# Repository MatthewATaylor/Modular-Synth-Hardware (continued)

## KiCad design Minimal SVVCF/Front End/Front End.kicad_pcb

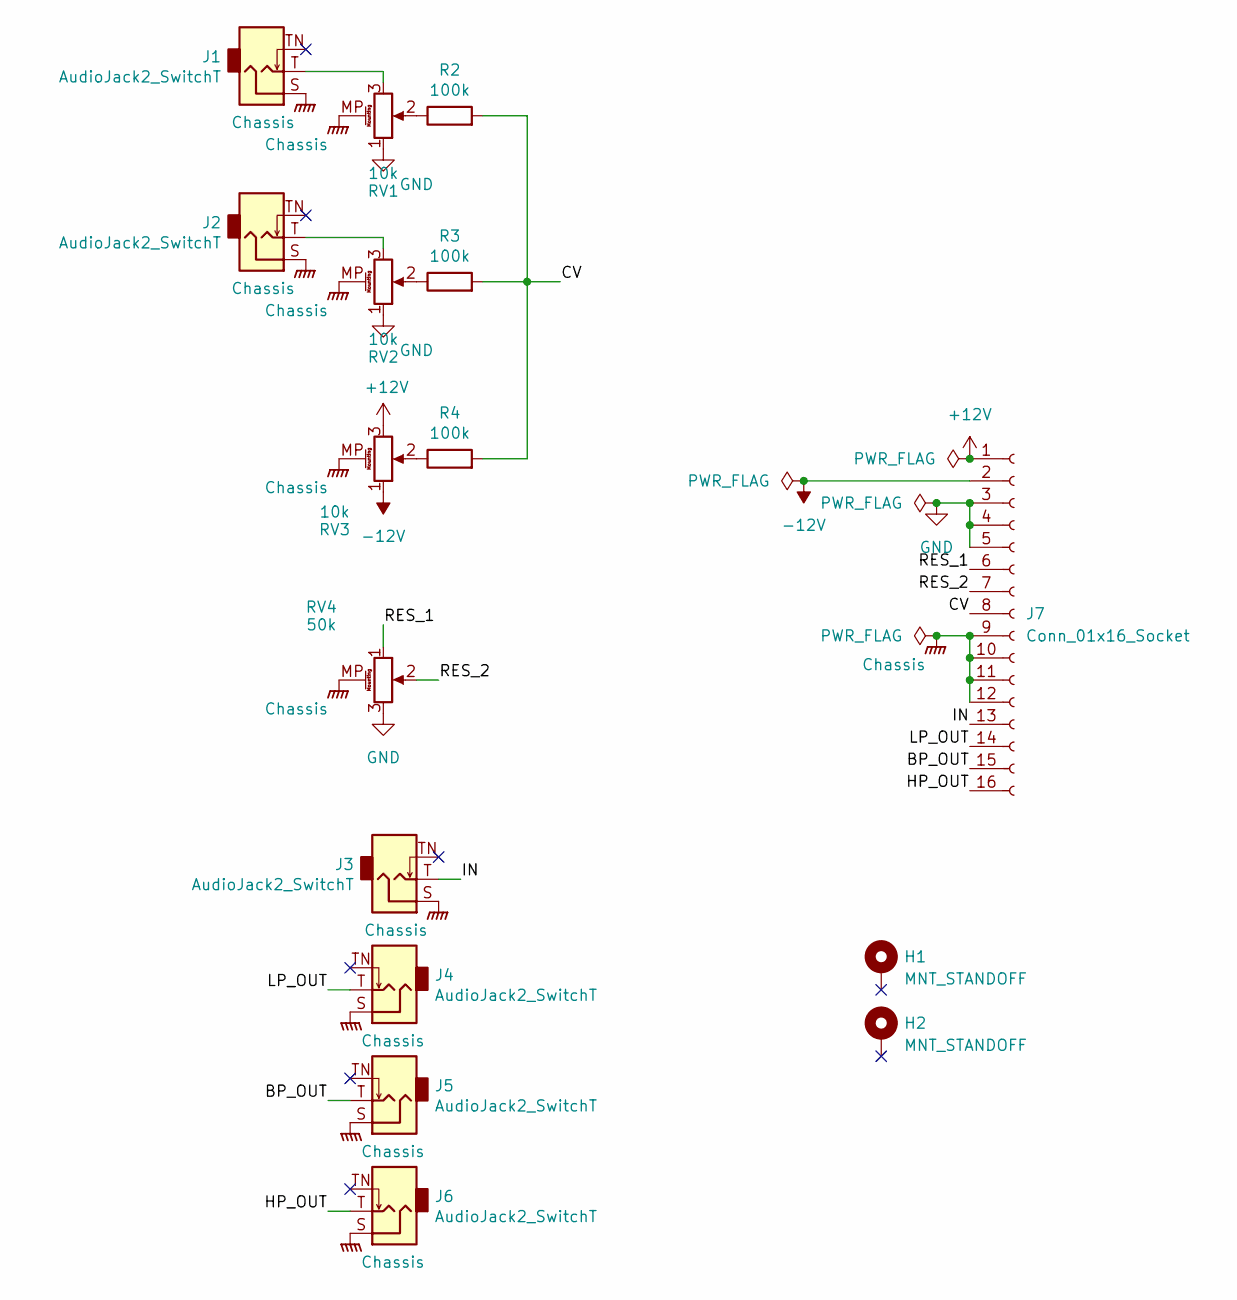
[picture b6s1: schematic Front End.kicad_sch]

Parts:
H1, H2: MNT_STANDOFF; MountingHole_Pitch7.5mm_Drill3.4mm
J1, J2, J3, J4, J5, J6: AudioJack2_SwitchT; Jack_3.5mm_QingPu_WQP-PJ398SM_Vertical_CircularHoles
J7: Conn_01x16_Socket; PinHeader_1x16_P2.54mm_Vertical
R2, R3, R4: 100k; R_Axial_DIN0207_L6.3mm_D2.5mm_P7.62mm_Horizontal
RV1, RV2, RV3: 10k; Potentiometer_Alpha_RD901F-40-00D_Single_Vertical_MP
RV4: 50k; Potentiometer_Alpha_RD901F-40-00D_Single_Vertical_MP

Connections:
+12V: J7.1, RV3.3
-12V: J7.2, RV3.1
/BP_OUT: J5.T, J7.15
/CV: J7.8, R2.2, R3.2, R4.2
/HP_OUT: J6.T, J7.16
/IN: J3.T, J7.13
/LP_OUT: J4.T, J7.14
/RES_1: J7.6, RV4.1
/RES_2: J7.7, RV4.2
Chassis: J1.S, J2.S, J3.S, J4.S, J5.S, J6.S, J7.9, J7.10, J7.11, J7.12, RV1.MP (MountPin), RV2.MP (MountPin), RV3.MP (MountPin), RV4.MP (MountPin)
GND: J7.3, J7.4, J7.5, RV1.1, RV2.1, RV4.3
unnamed: J1.T, RV1.3
unnamed: J2.T, RV2.3
unnamed: R2.1, RV1.2
unnamed: R3.1, RV2.2
unnamed: R4.1, RV3.2

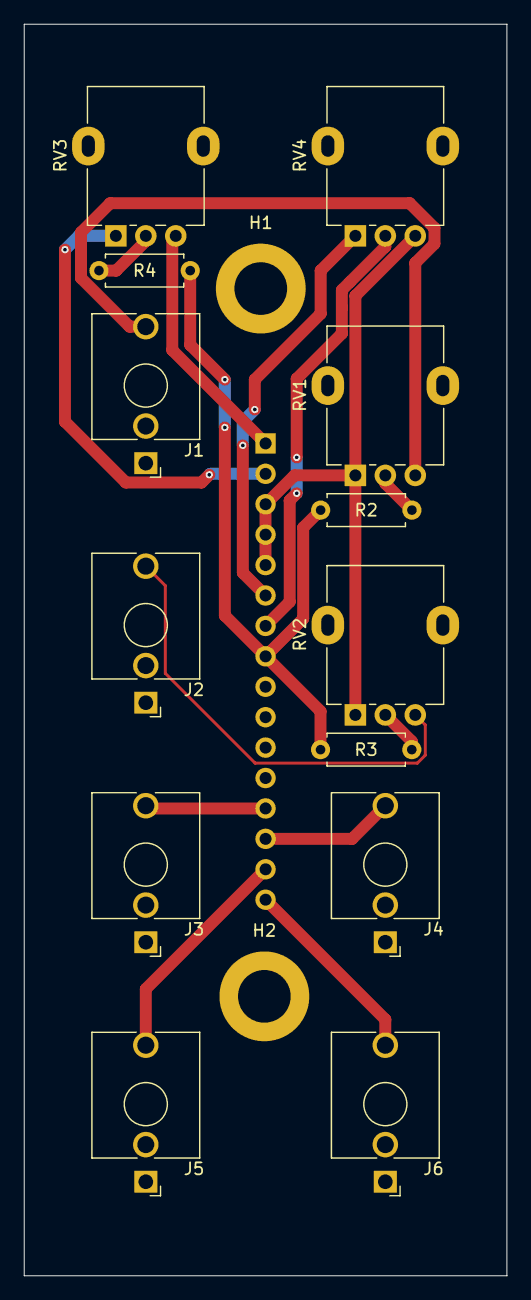
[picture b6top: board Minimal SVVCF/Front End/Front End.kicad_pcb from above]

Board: 2 copper layers, 40.3 x 104.5 mm, 16 parts (1 on the bottom side), 16 nets.

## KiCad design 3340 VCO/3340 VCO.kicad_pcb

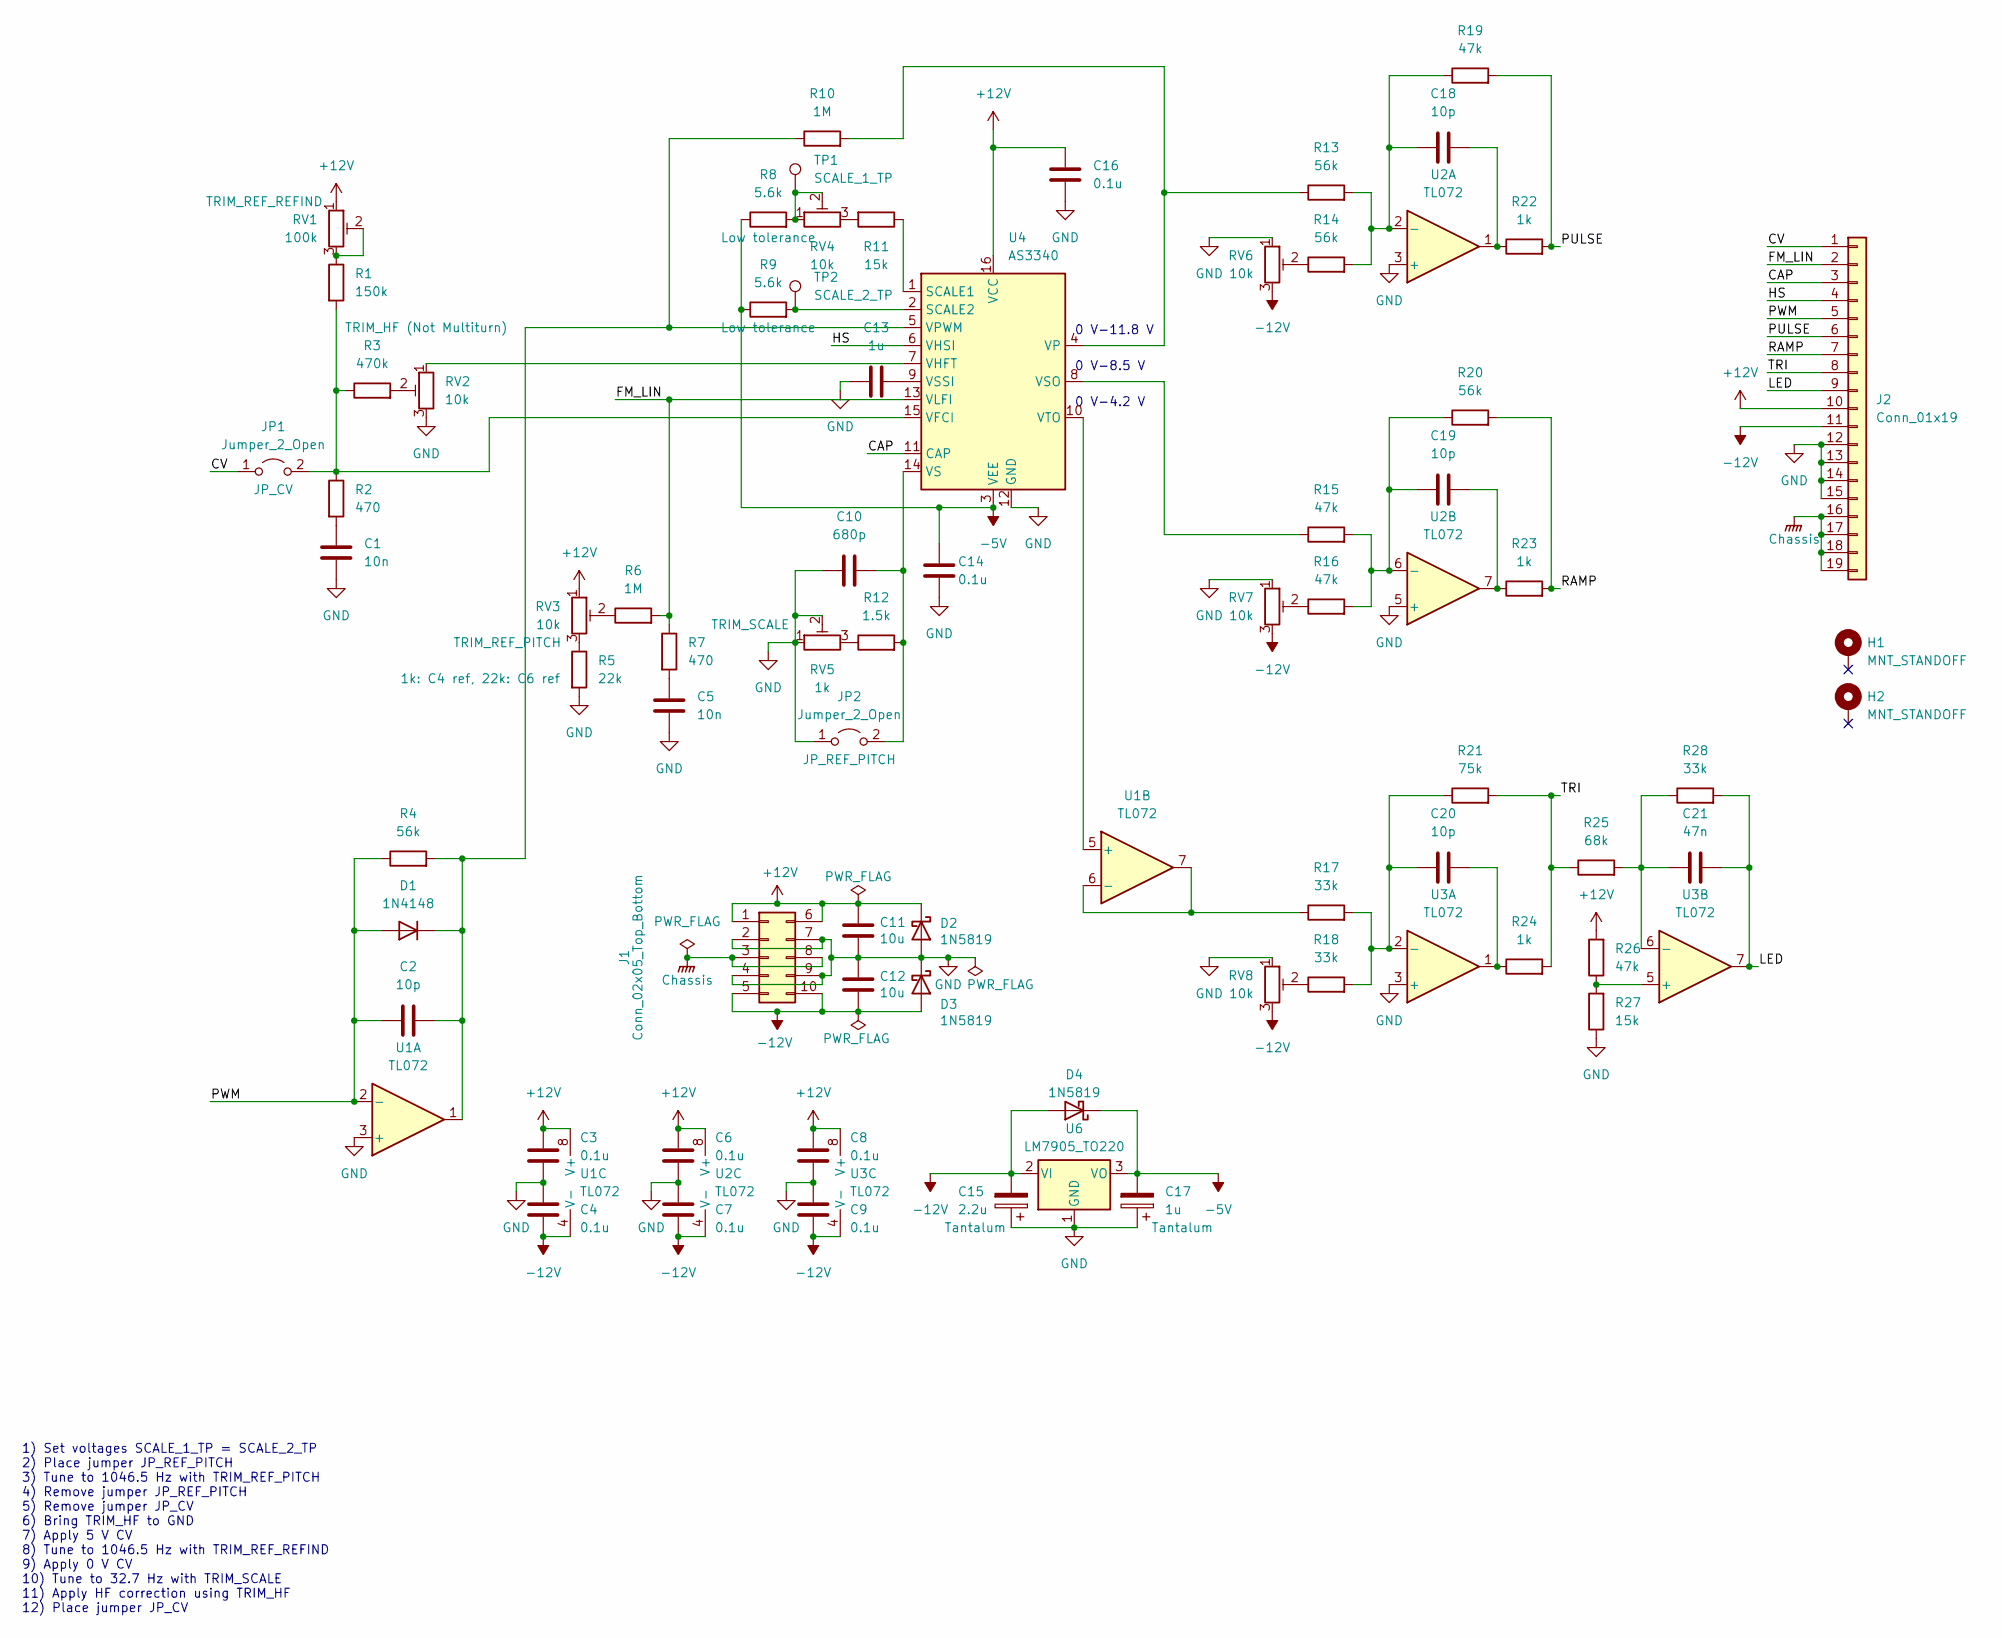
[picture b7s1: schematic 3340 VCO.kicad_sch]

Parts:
C1, C5: 10n; C_Disc_D5.5mm_W2.5mm_P2.50mm
C2, C18, C19, C20: 10p; C_Disc_D5.5mm_W2.5mm_P2.50mm
C3, C4, C6, C7, C8, C9, C14, C16: 0.1u; C_Disc_D5.5mm_W2.5mm_P2.50mm
C10: 680p; C_Disc_D5.5mm_W2.5mm_P2.50mm
C11, C12: 10u; C_Disc_D5.5mm_W4.0mm_P2.50mm
C13: 1u; C_Disc_D5.5mm_W4.0mm_P2.50mm
C15: 2.2u; CP_Radial_Tantal_D5.5mm_P2.50mm
C17: 1u; CP_Radial_Tantal_D5.0mm_P2.50mm
C21: 47n; C_Disc_D5.5mm_W2.5mm_P2.50mm
D1: 1N4148; D_DO-35_SOD27_P7.62mm_Horizontal
D2, D3, D4: 1N5819; D_DO-41_SOD81_P10.16mm_Horizontal
H1, H2: MNT_STANDOFF; MountingHole_Pitch7.5mm_Drill3.4mm
J1: Conn_02x05_Top_Bottom; Molex_Mini-Fit_Jr_5566-10A_2x05_P4.20mm_Vertical
J2: Conn_01x19; PinHeader_1x19_P2.54mm_Vertical
JP1, JP2: Jumper_2_Open; PinHeader_1x02_P2.54mm_Vertical
R1: 150k; R_Axial_DIN0207_L6.3mm_D2.5mm_P7.62mm_Horizontal
R2, R7: 470; R_Axial_DIN0207_L6.3mm_D2.5mm_P7.62mm_Horizontal
R3: 470k; R_Axial_DIN0207_L6.3mm_D2.5mm_P7.62mm_Horizontal
R4, R13, R14, R20: 56k; R_Axial_DIN0207_L6.3mm_D2.5mm_P7.62mm_Horizontal
R5: 22k; R_Axial_DIN0207_L6.3mm_D2.5mm_P7.62mm_Horizontal
R6, R10: 1M; R_Axial_DIN0207_L6.3mm_D2.5mm_P7.62mm_Horizontal
R8, R9: 5.6k; R_Axial_DIN0207_L6.3mm_D2.5mm_P7.62mm_Horizontal
R11, R27: 15k; R_Axial_DIN0207_L6.3mm_D2.5mm_P7.62mm_Horizontal
R12: 1.5k; R_Axial_DIN0207_L6.3mm_D2.5mm_P7.62mm_Horizontal
R15, R16, R19, R26: 47k; R_Axial_DIN0207_L6.3mm_D2.5mm_P7.62mm_Horizontal
R17, R18, R28: 33k; R_Axial_DIN0207_L6.3mm_D2.5mm_P7.62mm_Horizontal
R21: 75k; R_Axial_DIN0207_L6.3mm_D2.5mm_P7.62mm_Horizontal
R22, R23, R24: 1k; R_Axial_DIN0207_L6.3mm_D2.5mm_P7.62mm_Horizontal
R25: 68k; R_Axial_DIN0207_L6.3mm_D2.5mm_P7.62mm_Horizontal
RV1: 100k; Potentiometer_Bourns_3296W_Vertical
RV2: 10k; Potentiometer_Runtron_RM-065_Vertical
RV3, RV4, RV6, RV7, RV8: 10k; Potentiometer_Bourns_3296W_Vertical
RV5: 1k; Potentiometer_Bourns_3296W_Vertical
TP1: SCALE_1_TP; PinHeader_1x01_P2.54mm_Vertical
TP2: SCALE_2_TP; PinHeader_1x01_P2.54mm_Vertical
U1, U2, U3: TL072; DIP-8_W7.62mm_Socket
U4: AS3340; DIP-16_W7.62mm_Socket
U6: LM7905_TO220; TO-220-3_Vertical

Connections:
+12V: C3.2, C6.2, C8.2, C11.1, C16.2, D2.1 (K), J1.1, J1.6, J2.10, R26.2, RV1.1, RV3.1, U1.8 (V+), U2.8 (V+), U3.8 (V+), U4.16 (VCC)
-5V: C14.2, C17.2, D4.1 (K), R8.1, R9.1, U4.3 (VEE), U6.3 (VO)
-12V: C4.1, C7.1, C9.1, C12.2, C15.2, D3.2 (A), D4.2 (A), J1.5, J1.10, J2.11, RV6.3, RV7.3, RV8.3, U1.4 (V-), U2.4 (V-), U3.4 (V-), U6.2 (VI)
/CAP: J2.3, U4.11 (CAP)
/CV: J2.1, JP1.1 (A)
/FM_LIN: J2.2, R6.2, R7.1, U4.13 (VLFI)
/HS: J2.4, U4.6 (VHSI)
/LED: C21.2, J2.9, R28.2, U3.7
/PULSE: J2.6, R19.2, R22.2
/PWM: C2.1, D1.2 (A), J2.5, R4.1, U1.2 (-)
/RAMP: J2.7, R20.2, R23.2
/TRI: J2.8, R21.2, R24.2, R25.1
Chassis: J1.3, J1.8, J2.16, J2.17, J2.18, J2.19
GND: C1.2, C3.1, C4.2, C5.2, C6.1, C7.2, C8.1, C9.2, C10.1, C11.2, C12.1, C13.1, C14.1, C15.1, C16.1, C17.1, D2.2 (A), D3.1 (K), J1.2, J1.4, J1.7, J1.9, J2.12, J2.13, J2.14, J2.15, JP2.1 (A), R5.2, R27.1, RV2.3, RV5.1, RV5.2, RV6.1, RV7.1, RV8.1, U1.3 (+), U2.3 (+), U2.5 (+), U3.3 (+), U4.12 (GND), U6.1 (GND)
unnamed: C1.1, R2.2
unnamed: C5.1, R7.2
unnamed: C18.2, R22.1, U2.1
unnamed: C19.2, R23.1, U2.7
unnamed: C20.2, R24.1, U3.1
unnamed: C2.2, D1.1 (K), R4.2, R10.1, U1.1, U4.5 (VPWM)
unnamed: JP1.2 (B), R1.2, R2.1, R3.1, U4.15 (VFCI)
unnamed: C10.2, JP2.2 (B), R12.2, U4.14 (VS)
unnamed: R1.1, RV1.2, RV1.3
unnamed: R3.2, RV2.2
unnamed: R5.1, RV3.3
unnamed: R6.1, RV3.2
unnamed: R8.2, RV4.1, RV4.2, TP1.1
unnamed: R11.2, RV4.3
unnamed: R12.1, RV5.3
unnamed: R14.1, RV6.2
unnamed: R16.1, RV7.2
unnamed: R18.1, RV8.2
unnamed: U1.5 (+), U4.10 (VTO)
unnamed: R17.1, U1.6 (-), U1.7
unnamed: C18.1, R13.2, R14.2, R19.1, U2.2 (-)
unnamed: C19.1, R15.2, R16.2, R20.1, U2.6 (-)
unnamed: C20.1, R17.2, R18.2, R21.1, U3.2 (-)
unnamed: R26.1, R27.2, U3.5 (+)
unnamed: C21.1, R25.2, R28.1, U3.6 (-)
unnamed: R11.1, U4.1 (SCALE1)
unnamed: R9.2, TP2.1, U4.2 (SCALE2)
unnamed: RV2.1, U4.7 (VHFT)
unnamed: R10.2, R13.1, U4.4 (VP)
unnamed: R15.1, U4.8 (VSO)
unnamed: C13.2, U4.9 (VSSI)

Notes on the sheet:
0 V-11.8 V
0 V-8.5 V
0 V-4.2 V
1) Set voltages SCALE_1_TP = SCALE_2_TP 2) Place jumper JP_REF_PITCH 3) Tune to 1046.5 Hz with TRIM_REF_PITCH 4) Remove jumper JP_REF_PITCH 5) Remove jumper JP_CV 6) Bring TRIM_HF to GND 7) Apply 5 V CV 8) Tune to 1046.5 Hz with TRIM_REF_REFIND 9) Apply 0 V CV 10) Tune to 32.7 Hz with TRIM_SCALE 11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

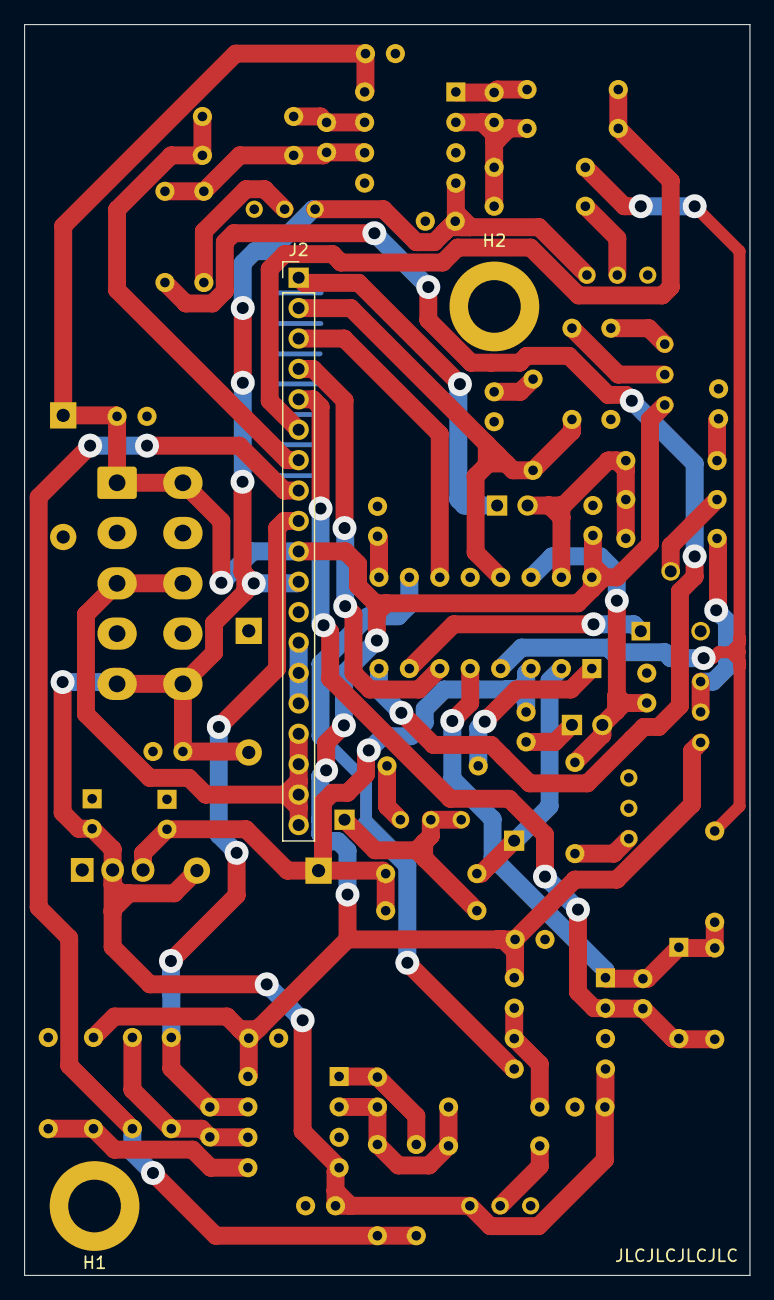
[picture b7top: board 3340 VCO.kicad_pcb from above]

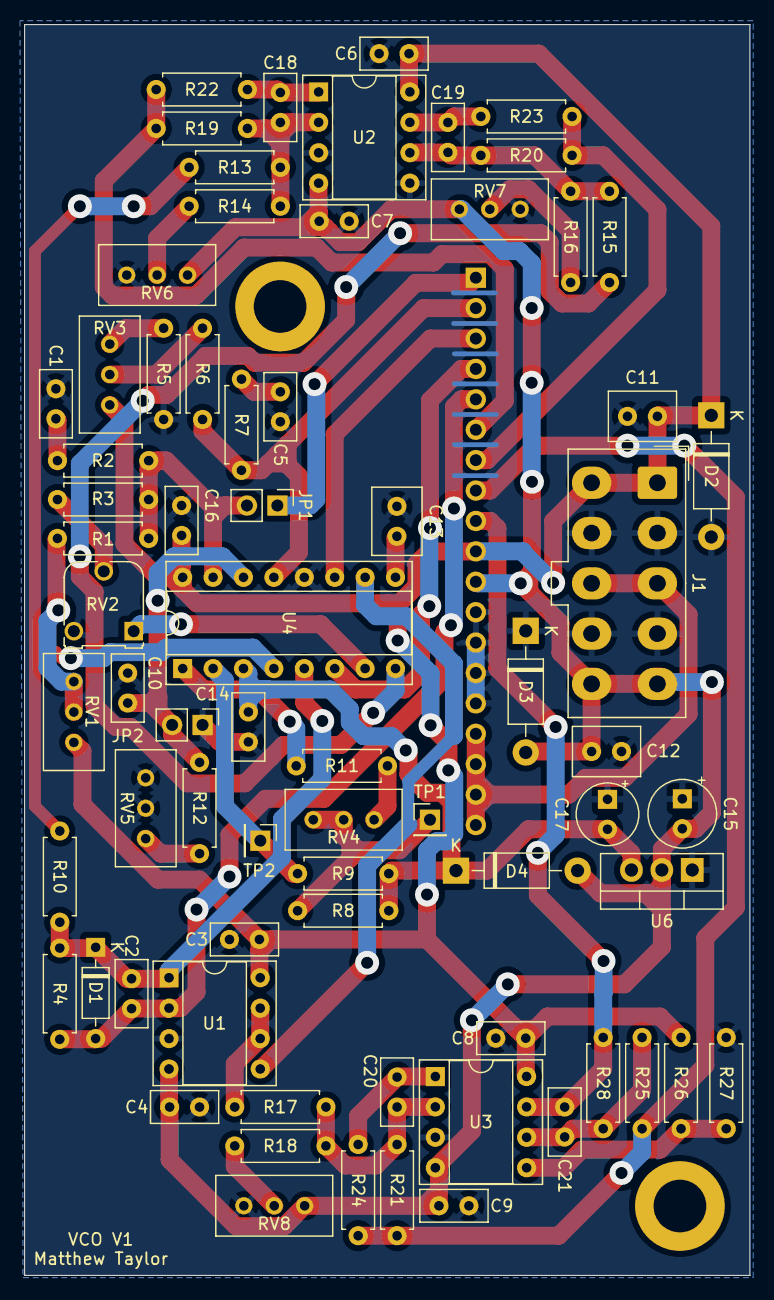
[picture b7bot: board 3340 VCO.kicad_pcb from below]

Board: 2 copper layers, 60.6 x 104.5 mm, 74 parts (71 on the bottom side), 45 nets.

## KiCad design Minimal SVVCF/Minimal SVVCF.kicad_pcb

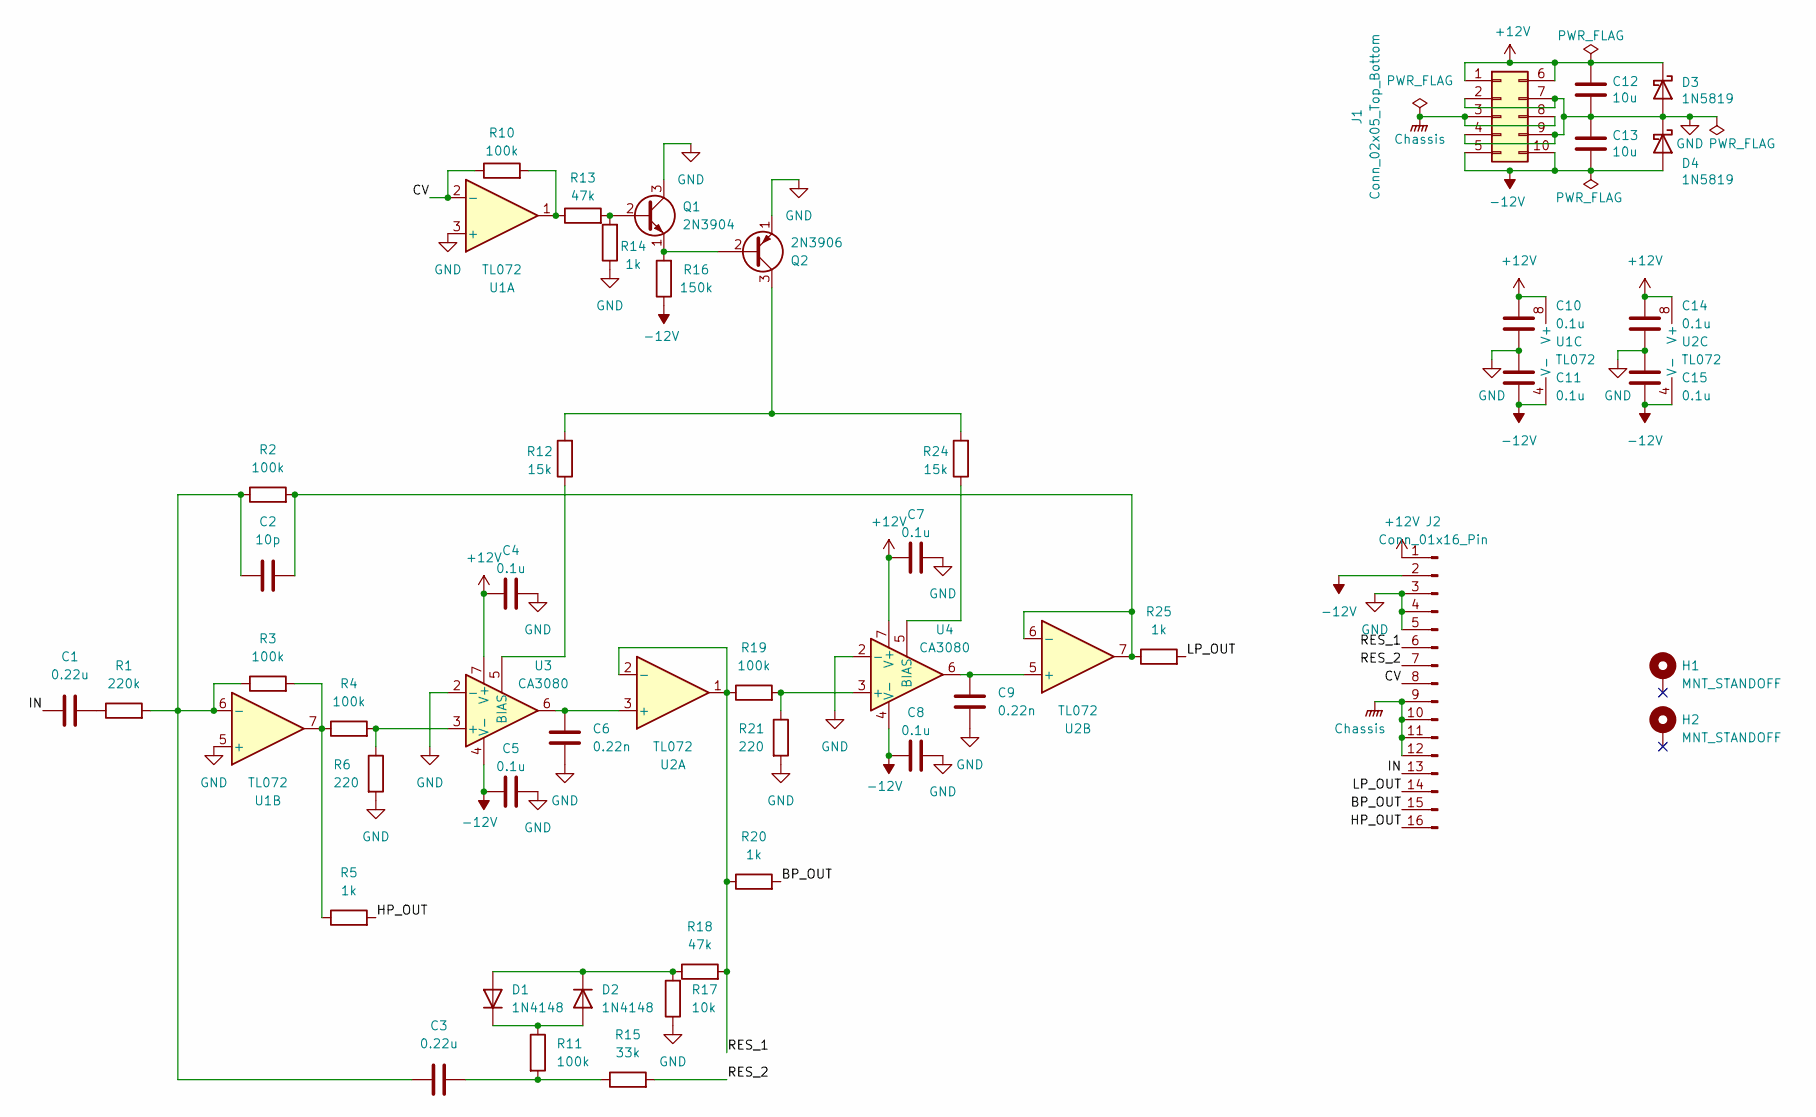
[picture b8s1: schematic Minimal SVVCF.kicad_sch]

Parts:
C1, C3: 0.22u; C_Disc_D5.5mm_W2.5mm_P2.50mm
C2: 10p; C_Disc_D5.5mm_W2.5mm_P2.50mm
C4, C5, C7, C8, C10, C11, C14, C15: 0.1u; C_Disc_D5.5mm_W2.5mm_P2.50mm
C6, C9: 0.22n; C_Disc_D5.5mm_W2.5mm_P2.50mm
C12, C13: 10u; C_Disc_D5.5mm_W4.0mm_P2.50mm
D1, D2: 1N4148; D_DO-35_SOD27_P7.62mm_Horizontal
D3, D4: 1N5819; D_DO-41_SOD81_P10.16mm_Horizontal
H1, H2: MNT_STANDOFF; MountingHole_Pitch7.5mm_Drill3.4mm
J1: Conn_02x05_Top_Bottom; Molex_Mini-Fit_Jr_5566-10A_2x05_P4.20mm_Vertical
J2: Conn_01x16_Pin; PinHeader_1x16_P2.54mm_Vertical
Q1: 2N3904; TO-92_HandSolder
Q2: 2N3906; TO-92_HandSolder
R1: 220k; R_Axial_DIN0207_L6.3mm_D2.5mm_P7.62mm_Horizontal
R2, R3, R4, R10, R11, R19: 100k; R_Axial_DIN0207_L6.3mm_D2.5mm_P7.62mm_Horizontal
R5, R14, R20, R25: 1k; R_Axial_DIN0207_L6.3mm_D2.5mm_P7.62mm_Horizontal
R6, R21: 220; R_Axial_DIN0207_L6.3mm_D2.5mm_P7.62mm_Horizontal
R12, R24: 15k; R_Axial_DIN0207_L6.3mm_D2.5mm_P7.62mm_Horizontal
R13, R18: 47k; R_Axial_DIN0207_L6.3mm_D2.5mm_P7.62mm_Horizontal
R15: 33k; R_Axial_DIN0207_L6.3mm_D2.5mm_P7.62mm_Horizontal
R16: 150k; R_Axial_DIN0207_L6.3mm_D2.5mm_P7.62mm_Horizontal
R17: 10k; R_Axial_DIN0207_L6.3mm_D2.5mm_P7.62mm_Horizontal
U1, U2: TL072; DIP-8_W7.62mm_Socket
U3, U4: CA3080; DIP-8_W7.62mm_Socket

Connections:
+12V: C4.1, C7.1, C10.2, C12.1, C14.2, D3.1 (K), J1.1, J1.6, J2.1, U1.8 (V+), U2.8 (V+), U3.7 (V+), U4.7 (V+)
-12V: C5.1, C8.1, C11.1, C13.2, C15.1, D4.2 (A), J1.5, J1.10, J2.2, R16.1, U1.4 (V-), U2.4 (V-), U3.4 (V-), U4.4 (V-)
/BP_OUT: J2.15, R20.2
/CV: J2.8, R10.1, U1.2 (-)
/HP_OUT: J2.16, R5.2
/IN: C1.1, J2.13
/LP_OUT: J2.14, R25.2
/RES_1: J2.6, R18.2, R19.1, R20.1, U2.1, U2.2 (-)
/RES_2: J2.7, R15.2
Chassis: J1.3, J1.8, J2.9, J2.10, J2.11, J2.12
GND: C4.2, C5.2, C6.2, C7.2, C8.2, C9.2, C10.1, C11.2, C12.2, C13.1, C14.1, C15.2, D3.2 (A), D4.1 (K), J1.2, J1.4, J1.7, J1.9, J2.3, J2.4, J2.5, Q1.3 (C), Q2.1 (E), R6.2, R14.1, R17.1, R21.2, U1.3 (+), U1.5 (+), U3.2 (-), U4.2 (-)
unnamed: C1.2, R1.1
unnamed: C3.2, R11.2, R15.1
unnamed: D1.2 (A), D2.1 (K), R17.2, R18.1
unnamed: D1.1 (K), D2.2 (A), R11.1
unnamed: Q1.2 (B), R13.2, R14.2
unnamed: Q1.1 (E), Q2.2 (B), R16.2
unnamed: Q2.3 (C), R12.2, R24.2
unnamed: R3.2, R4.1, R5.1, U1.7
unnamed: R10.2, R13.1, U1.1
unnamed: C2.1, C3.1, R1.2, R2.1, R3.1, U1.6 (-)
unnamed: C6.1, U2.3 (+), U3.6
unnamed: C9.1, U2.5 (+), U4.6
unnamed: C2.2, R2.2, R25.1, U2.6 (-), U2.7
unnamed: R4.2, R6.1, U3.3 (+)
unnamed: R12.1, U3.5 (BIAS)
unnamed: R19.2, R21.1, U4.3 (+)
unnamed: R24.1, U4.5 (BIAS)

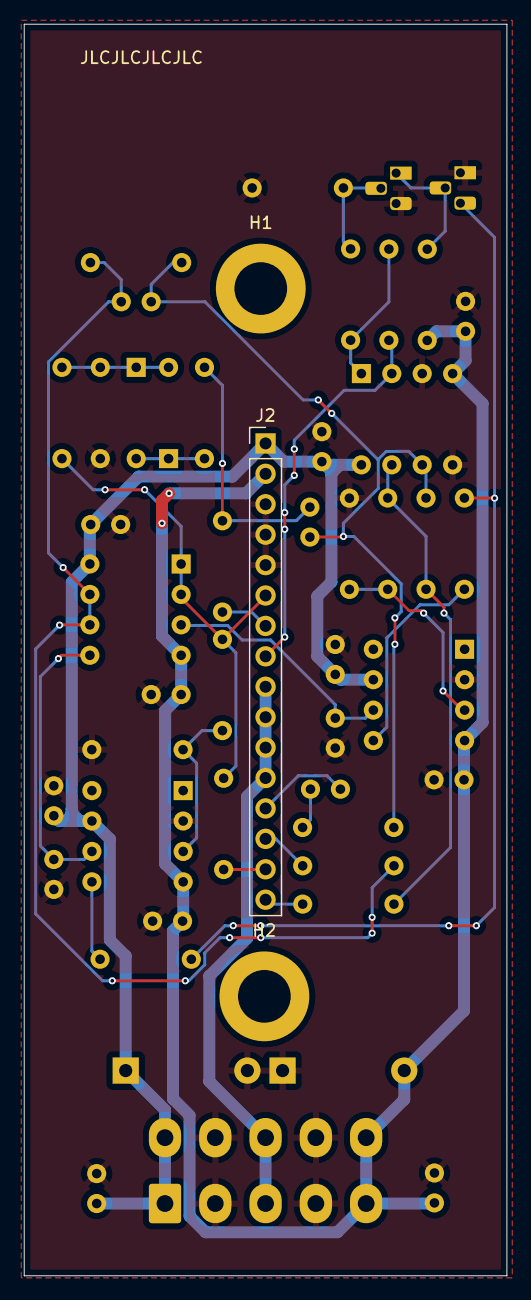
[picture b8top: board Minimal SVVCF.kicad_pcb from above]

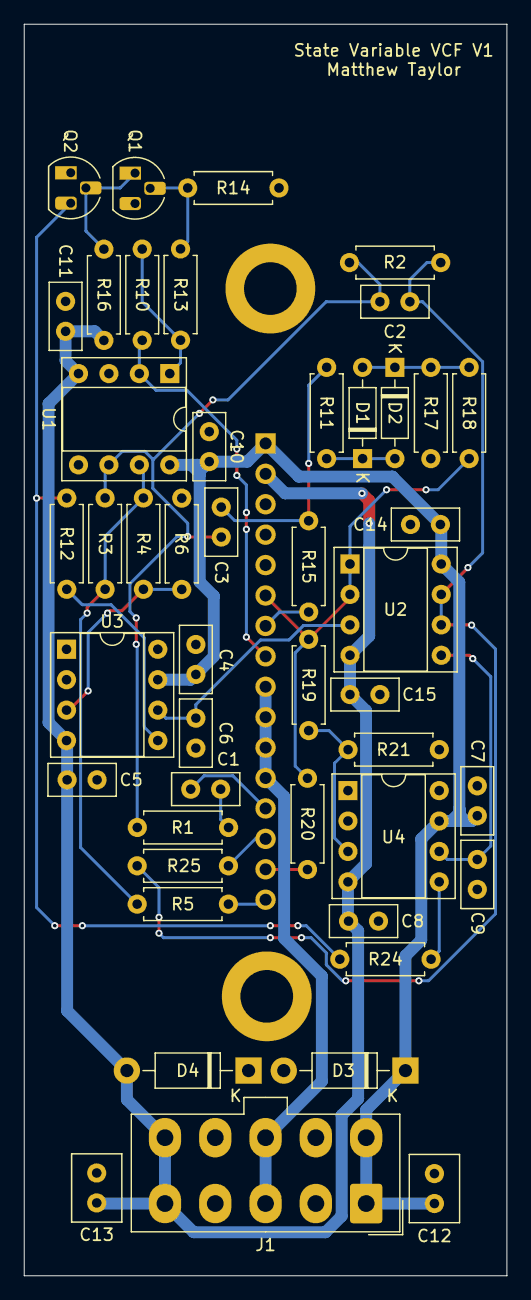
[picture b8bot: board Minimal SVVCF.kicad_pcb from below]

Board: 2 copper layers, 40.3 x 104.5 mm, 49 parts (46 on the bottom side), 28 nets.

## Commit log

2021-12-30 Add VCO
2021-12-30 Add VCA
2021-12-30 Remove VCA
2021-12-30 Add VCA readme
2021-12-30 Add panel solder mask
2021-12-30 Fix VCO design rule errors
2021-12-30 Fix problems in VCO schematic
2021-12-30 Apply VCO changes to PCB layout
2021-12-30 Create LICENSE
2021-12-30 Change some VCO trim pot footprints
2021-12-30 Add WIP delay
2021-12-30 Add delay daisy chaining switches and readme
2021-12-30 Remove auto save file
2021-12-30 Add Controller
2021-12-30 Add Envelope Generator
2021-12-30 Add EG readme
2021-12-30 Add Power Supply
2021-12-30 Add Power Supply readme
2021-12-30 Add VCF
2021-12-30 Add Mixer
2021-12-31 Add Mult
2022-01-27 Finish delay PCB
2022-01-28 Add white noise
2022-01-29 Add delay panel
2022-01-31 Start simplified controller
2022-02-01 Finish simplified controller
2022-02-01 Flip VCO LEDs
2022-02-02 Add Offset
2022-05-25 Add SKVCF
2022-05-25 Add readmes
2023-07-13 New modules, small updates
2023-07-15 Update AR design
2023-07-16 Remove inverted EG out
2023-07-16 Simplify EG
2023-07-16 Change component note labels
2023-07-16 Complete 3340 VCO schematic
2023-07-16 Clean up 3340 VCO schematic
2023-07-16 Minor EG updates
2023-07-16 Change LED resistor values
2023-07-16 Remove 5V from PSU
2023-07-16 Change EG LED filter capacitor
2023-07-18 Add output module
2023-07-19 Update power connectors
2023-07-25 Rework output module, add VCA pan, tweak EG/VCO
2023-07-25 Add EG button
2023-07-25 Add pot mounting pins to EG
2023-07-25 Replace AR with decay
2023-07-25 Start MIDI interface
2023-08-03 Finish MIDI interface schematics, minor EG/VCO changes
2023-08-03 Redo mixer schematic
2023-08-03 Add stereo mixer
2023-08-03 Update decay caps, fix ERC issues
2023-08-04 Update PSU output
2023-08-05 Fix VCO ERC issues
2023-08-05 Fix VCA ERC issues, small VCA updates
2023-08-05 Fix out module ERC issues
2023-08-05 Fix EG ERC issues
2023-08-05 Fix MIDI I/F ERC issues, add tuner OVP
2023-08-05 Fix mixer ERC issues
2023-08-09 Assign footprints
2023-08-21 Place PSU components on PCB
2023-08-31 Begin routing PSU, upgrade to KiCad 7
2023-08-31 Fix schematic parity
2023-08-31 Fix DRC issues
2023-08-31 Finish routing
2023-08-31 Create additional filled zones
2023-09-01 Finish up power supply
2023-09-01 Create separate front end VCO board
2023-09-01 Add -5V regulator
2023-09-01 Add VCO front end board
2023-09-01 Add vias to PSU screw holes
2023-09-01 Remove tab connections
2023-09-05 Manage thermal reliefs
2023-09-05 Remove tab pins
2023-09-05 Arrange VCO front end components
2023-09-09 Update power connectors, minor fixes
2023-09-10 Add precision R and C notes, update -5V regulator
2023-09-12 Update VCO capacitor selection
2023-09-20 Update gitignore, VCO changes
2023-09-20 Readd all unignored files
2024-03-06 Finish VCO
2024-03-16 Migrate to Linux
2024-03-22 Create VCA front end project
2024-03-28 Finish VCA PCB
2024-03-29 Add VCA and VCO front panels
2024-05-24 Start MIDI interface board
2025-01-13 New MIDI controller, new envelope generator
2025-01-21 New VCLPF and Out
2025-01-24 Finish main set of revisions
2025-01-31 Finish filter, mixer, mult
2025-02-28 Begin revised delay
2025-03-08 Finish diode ladder filter
2025-04-06 PCB fixes and cleanup
2025-04-17 Add Decay, clean up gerbers
2025-04-25 Add spring reverb
2025-04-26 Small changes
